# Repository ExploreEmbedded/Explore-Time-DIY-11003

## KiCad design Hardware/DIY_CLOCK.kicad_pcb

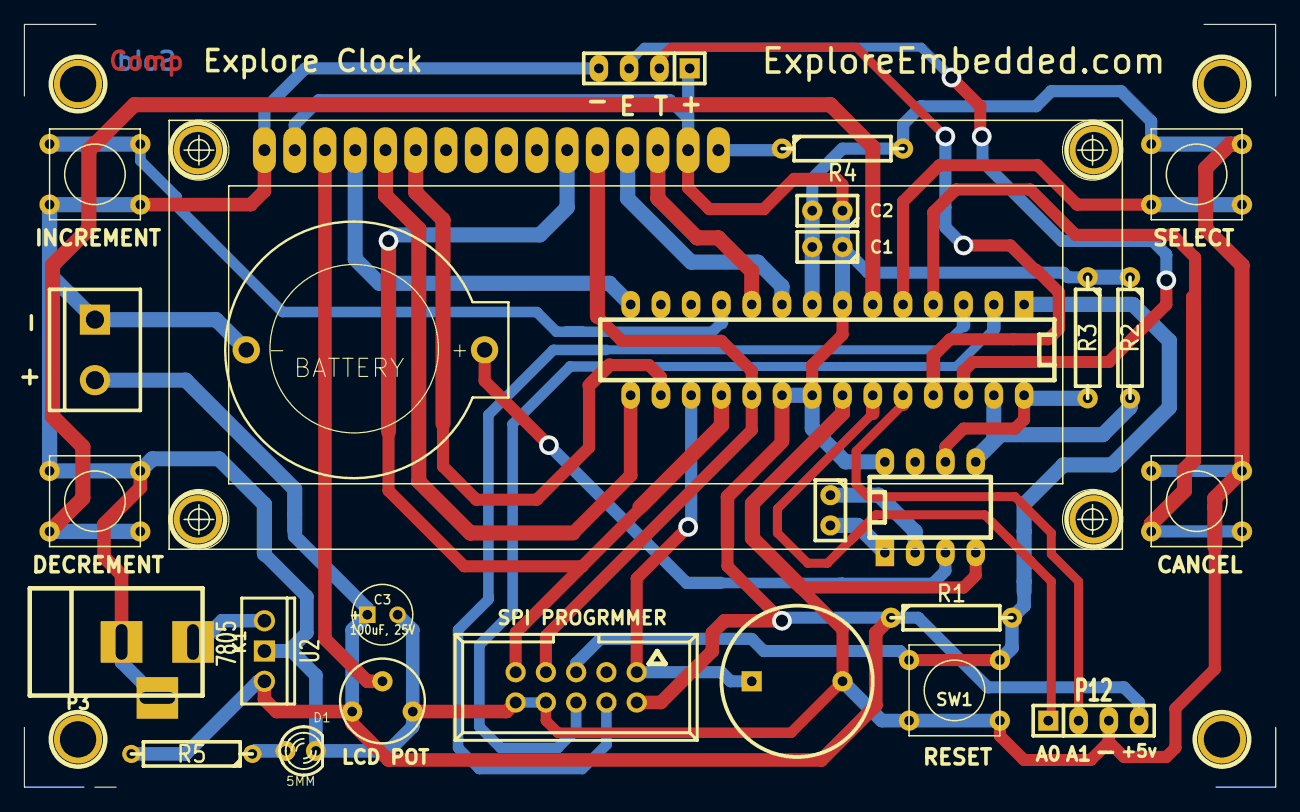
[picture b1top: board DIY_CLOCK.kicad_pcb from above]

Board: 2 copper layers, 105.0 x 64.0 mm, 35 parts (0 on the bottom side), 30 nets.

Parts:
BT1: BATTERY; BATT_rtc_XL
C1, C2: 0.1uF; C1
C3: 100uF, 25V; C1V5
D1: 5MM; LED-3MM
IC1: ATMEGA8-P; DIP-28__300_ELL
K1: BARREL; BARREL_JACK
LCD1: LCD_2X16_SIL; lcd_2x16_led_backlight-HY-1602F
P1: CONN_5X2; VASCH5x2
P2: Power; bornier2
P3, P4, P5, P6, P7, P8, P9, P10: CONN_1; 1pin
P11, P12: CONN_4; SIL-4
R1, R2, R3: 10K; R4
R4: 2.2K; R4
R5: 470; R4
RV1: POT; RV2
SP1: SPEAKER; BUZ3-5
SW1: SPST; SW_PUSH_SMALL
SW2: INC; SW_PUSH_SMALL
SW3: DEC; SW_PUSH_SMALL
SW4: SEL; SW_PUSH_SMALL
SW5: CAN; SW_PUSH_SMALL
U1: DS1307; DIP-8__300_ELL
U2: 7805; LM78XXV
X1: CRYSTAL; C1

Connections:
+5V: C1.1, C2.1, C3.1, IC1.7, IC1.20, IC1.21, LCD1.2, LCD1.15, P1.2, P2.2, P11.1, P12.4, R1.1, R2.1, R3.1, R5.2, RV1.1, U1.8, U2.VO
/A0: IC1.23, P12.1
/A1: IC1.24, P12.2
/Echo: IC1.26, P11.3
/MISO: IC1.18, LCD1.11, P1.9
/MOSI: IC1.17, P1.1, SP1.1
/RST: IC1.1, P1.5, R1.2, SW1.2
/RX: IC1.2, P1.6
/SCK: IC1.19, LCD1.12, P1.7
/TX: IC1.3, P1.4
/Trig: IC1.25, P11.2
GND: BT1.2, C1.2, C2.2, C3.2, D1.2, IC1.8, IC1.22, K1.2, K1.3, LCD1.1, P1.8, P1.10, P2.1, P11.4, P12.3, R4.2, RV1.3, SP1.2, SW1.1, SW2.1, SW3.1, SW4.1, SW5.1, U1.4, U2.GND
unnamed: IC1.6, SW3.2
unnamed: BT1.1, U1.3
unnamed: U1.1, X1.2
unnamed: IC1.11, SW2.2
unnamed: IC1.5, SW4.2
unnamed: IC1.4, SW5.2
unnamed: IC1.28, R3.2, U1.6
unnamed: IC1.27, R2.2, U1.5
unnamed: LCD1.3, RV1.2
unnamed: IC1.10, LCD1.14
unnamed: U1.2, X1.1
unnamed: IC1.9, LCD1.13
unnamed: K1.1, U2.VI
unnamed: D1.1, R5.1
unnamed: LCD1.16, R4.1
unnamed: IC1.14, LCD1.4
unnamed: IC1.16, LCD1.6
unnamed: IC1.15, LCD1.5

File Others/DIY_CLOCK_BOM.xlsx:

Id | Designator | Package | Quantity | Designation | Supplier and ref
1 | P1 | VASCH5x2 | 1 | CONN_5X2
2 | RV1 | RV2 | 1 | POT
3 | R4 | R4 | 1 | 2.2K
4 | R3,R2,R1 | R4 | 3 | 10K
5 | U1 | DIP-8__300_ELL | 1 | DS1307
6 | IC1 | DIP-28__300_ELL | 1 | ATMEGA8-P
7 | X1 | C1 | 1 | CRYSTAL
8 | C2,C1 | C1 | 2 | 0.1uF
9 | BT1 | BATT_rtc_XL | 1 | BATTERY
10 | LCD1 | lcd_2x16_led_backlight-HY-1602F | 1 | LCD_2X16_SIL
11 | SW3 | SW_PUSH_SMALL | 1 | DEC
12 | SW5 | SW_PUSH_SMALL | 1 | CAN
13 | SW2 | SW_PUSH_SMALL | 1 | INC
14 | SW4 | SW_PUSH_SMALL | 1 | SEL
15 | SW1 | SW_PUSH_SMALL | 1 | SPST
16 | P2 | bornier2 | 1 | Power
17 | P3,P4,P5,P6,P7,P8,P9,P10 | 1pin | 8 | CONN_1
18 | SP1 | BUZ3-5 | 1 | SPEAKER
19 | P12,P11 | SIL-4 | 2 | CONN_4
20 | R5 | R4 | 1 | 470
21 | D1 | LED-3MM | 1 | 5MM
22 | C3 | C1V5 | 1 | 100uF, 25V
23 | K1 | BARREL_JACK | 1 | BARREL
24 | U2 | LM78XXV | 1 | 7805

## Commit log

2015-05-21 Added files
2015-06-05 Firmware for Explore time
    Basic code is done. Enhancements needed to be done
2015-06-08 Firmware Updated
2015-06-09 Explore Time
2015-06-15 Added firmware for Distance Meter
